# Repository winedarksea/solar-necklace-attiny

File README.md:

# solar-necklace-attiny
Solar Necklace Schematics and ATTiny code

There are two versions here, the original lightsaber necklace and the newer moissanite based version. The attiny code is for the latter.

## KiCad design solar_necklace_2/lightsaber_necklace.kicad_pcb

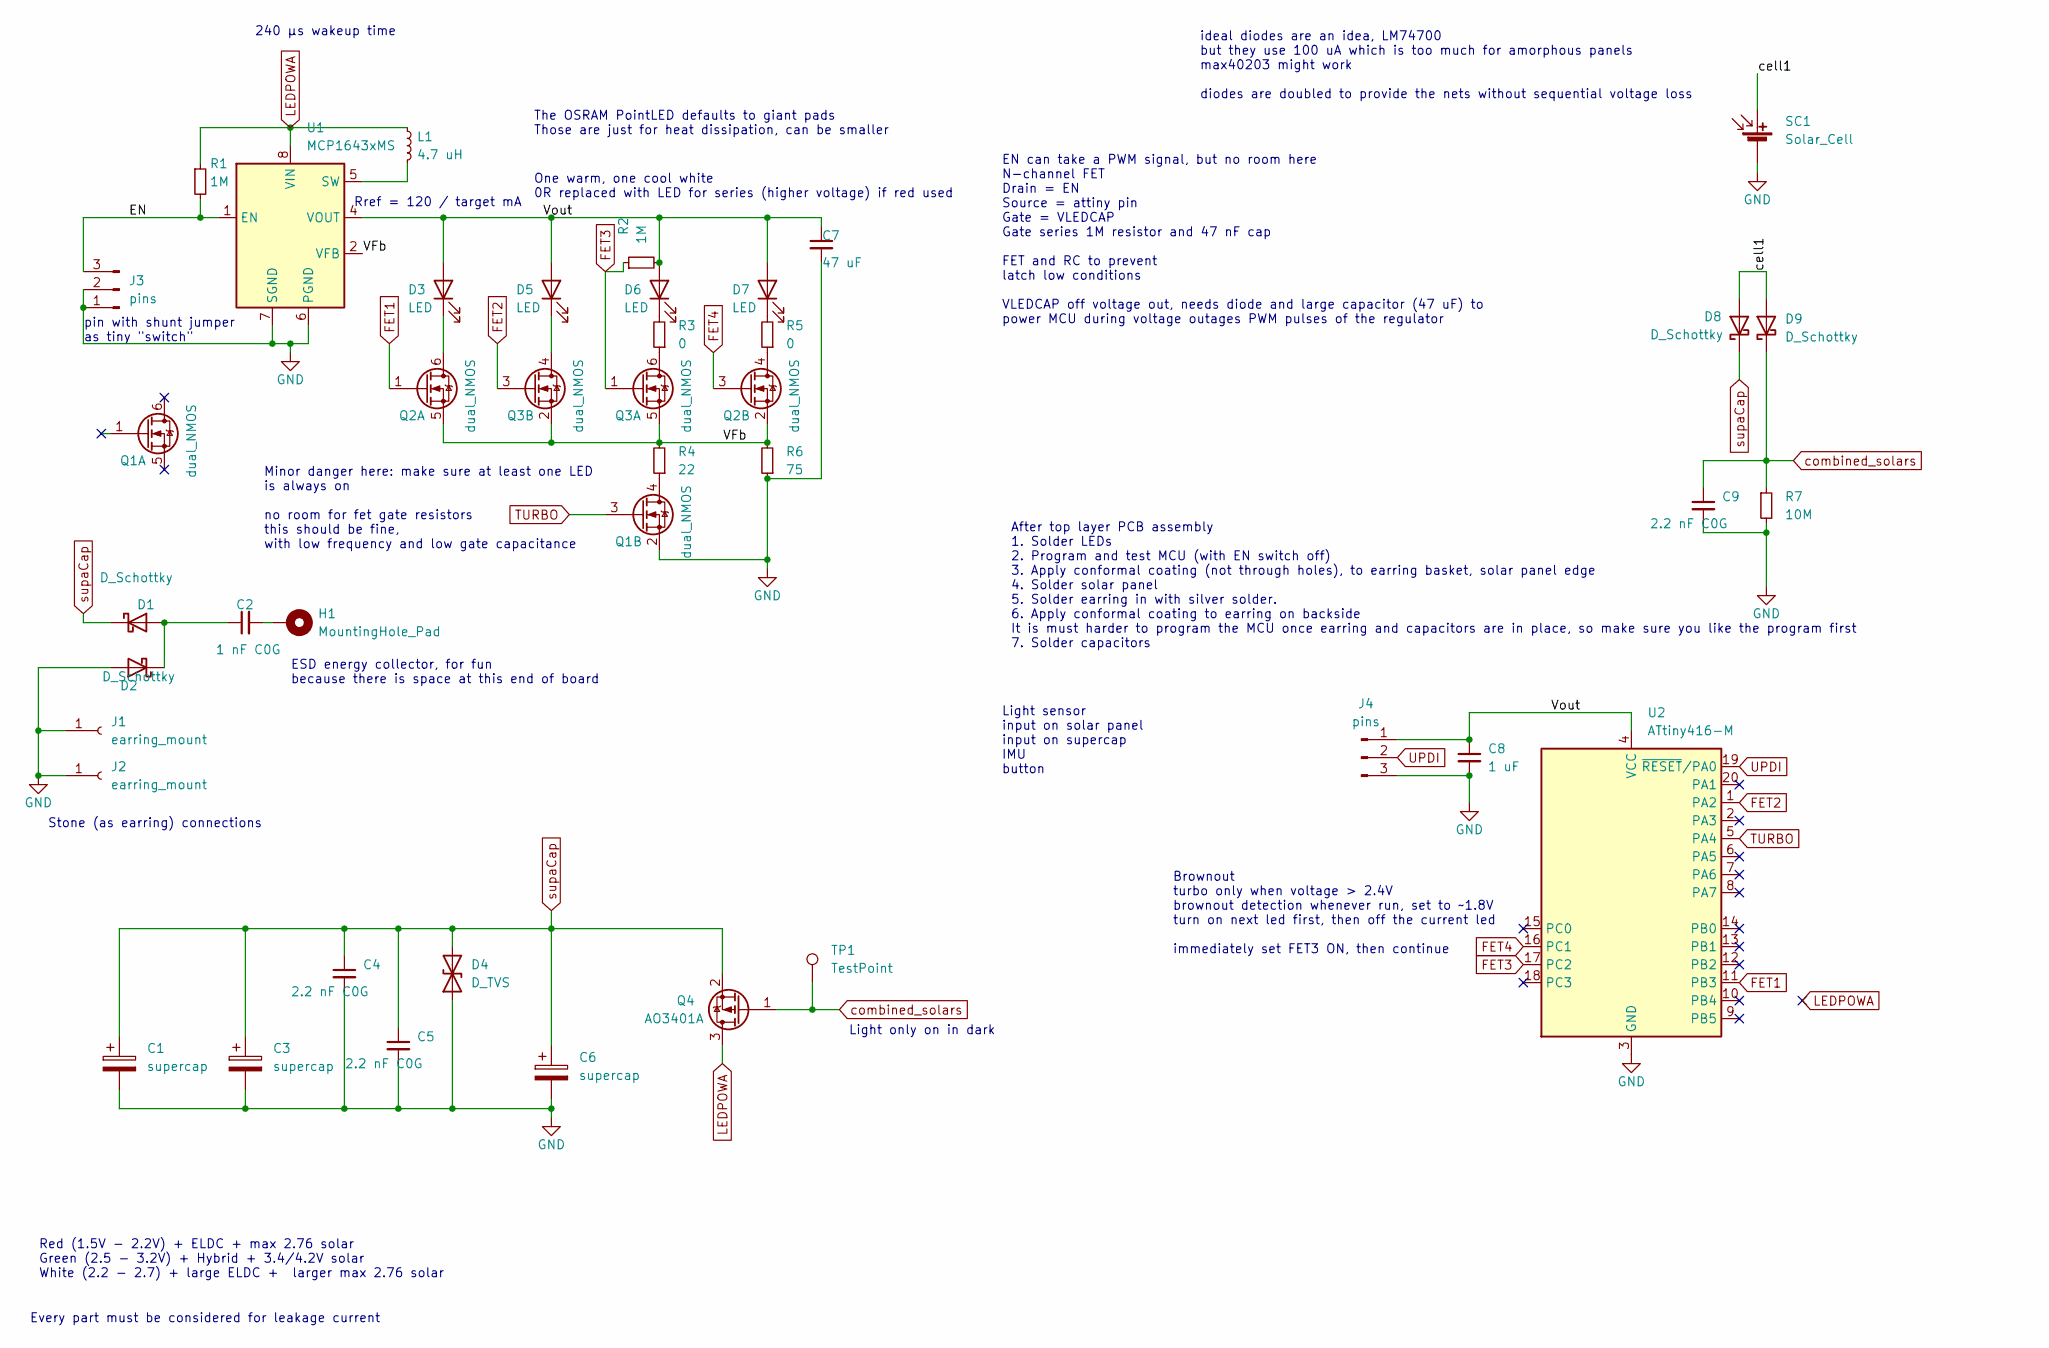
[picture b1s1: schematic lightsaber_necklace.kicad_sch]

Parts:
C1, C3, C6: supercap; C_Rect_L11.5mm_W9.8mm_P10.00mm_MKT
C2: 1 nF C0G; C_1206_3216Metric
C4, C5, C9: 2.2 nF C0G; C_0805_2012Metric
C7: 47 uF; C_1206_3216Metric
C8: 1 uF; C_0402_1005Metric
D1, D2, D8, D9: D_Schottky; D_SOD-323
D3, D5: LED; LED_1206_3216Metric_ReverseMount_Hole1.8x2.4mm
D4: D_TVS; D_SOD-523
D6, D7: LED; LED_Osram_Lx_P47F_D2mm_ReverseMount
H1: MountingHole_Pad; MountingHole_2.2mm_M2_DIN965_Pad
J1, J2: earring_mount; SolderWire-0.5sqmm_1x01_D0.9mm_OD2.1mm
J3, J4: pins; PinHeader_1x03_P1.27mm_Vertical
L1: 4.7 uH; L_0603_1608Metric
Q1, Q2, Q3: dual_NMOS; SOT-23-6
Q4: AO3401A; SOT-23
R1, R2: 1M; R_0402_1005Metric
R3, R5: 0; R_0603_1608Metric
R4: 22; R_0402_1005Metric
R6: 75; R_0603_1608Metric
R7: 10M; R_0402_1005Metric
SC1: Solar_Cell; PinHeader_1x02_P2.00mm_Vertical
TP1: TestPoint; TestPoint_Pad_D1.0mm
U1: MCP1643xMS; MSOP-8_3x3mm_P0.65mm
U2: ATtiny416-M; VQFN-20-1EP_3x3mm_P0.4mm_EP1.7x1.7mm

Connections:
/EN: J3.3, R1.2, U1.1 (EN)
/VFb: Q2.2 (S), Q2.5 (S), Q3.2 (S), Q3.5 (S), R4.2, R6.2, U1.2 (VFB)
/Vout: C7.1, C8.1, D3.2 (A), D5.2 (A), D6.2 (A), D7.2 (A), J4.1, R2.2, U1.4 (VOUT), U2.4 (VCC)
/cell1: D8.2 (A), D9.2 (A), SC1.1 (+)
FET1: Q2.1 (G), U2.11 (PB3)
FET2: Q3.3 (G), U2.1 (PA2)
FET3: Q3.1 (G), R2.1, U2.17 (PC2)
FET4: Q2.3 (G), U2.16 (PC1)
GND: C1.2, C3.2, C4.2, C5.2, C6.2, C7.2, C8.2, C9.2, D2.2 (A), D4.1 (A1), J1.1, J2.1, J3.1, J3.2, J4.3, Q1.2 (S), R6.1, R7.2, SC1.2 (-), U1.6 (PGND), U1.7 (SGND), U2.3 (GND), U2.21 (GND)
LEDPOWA: L1.1, Q4.3 (D), R1.1, U1.8 (VIN)
unnamed: C2.2, H1.1
unnamed: C2.1, D1.2 (A), D2.1 (K)
unnamed: D3.1 (K), Q2.6 (D)
unnamed: D5.1 (K), Q3.4 (D)
unnamed: D6.1 (K), R3.2
unnamed: D7.1 (K), R5.2
unnamed: Q1.4 (D), R4.1
unnamed: Q2.4 (D), R5.1
unnamed: Q3.6 (D), R3.1
unnamed: L1.2, U1.5 (SW)
TURBO: Q1.3 (G), U2.5 (PA4)
UPDI: J4.2, U2.19 (~RESET/PA0)
combined_solars: C9.1, D9.1 (K), Q4.1 (G), R7.1, TP1.1
supaCap: C1.1, C3.1, C4.1, C5.1, C6.1, D1.1 (K), D4.2 (A2), D8.1 (K), Q4.2 (S)

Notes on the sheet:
ideal diodes are an idea, LM74700 but they use 100 uA which is too much for amorphous panels max40203 might work diodes are doubled to provide the nets without sequential voltage loss
Every part must be considered for leakage current
EN can take a PWM signal, but no room here N-channel FET Drain = EN Source = attiny pin Gate = VLEDCAP Gate series 1M resistor and 47 nF cap FET and RC to prevent latch low conditions VLEDCAP off voltage out, needs diode and large capacitor (47 uF) to power MCU during voltage outages PWM pulses of 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
Red (1.5V - 2.2V) + ELDC + max 2.76 solar Green (2.5 - 3.2V) + Hybrid + 3.4/4.2V solar White (2.2 - 2.7) + large ELDC + larger max 2.76 solar
Light only on in dark
The OSRAM PointLED defaults to giant pads Those are just for heat dissipation, can be smaller
Rref = 120 / target mA
After top layer PCB assembly 1. Solder LEDs 2. Program and test MCU (with EN switch off) 3. Apply conformal coating (not through holes), to earring basket, solar panel edge 4. Solder solar panel 5. Solder earring in with silver solder. 6. Apply conformal coating to earring on backside It is must ha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
Minor danger here: make sure at least one LED is always on no room for fet gate resistors this should be fine, with low frequency and low gate capacitance
One warm, one cool white 0R replaced with LED for series (higher voltage) if red used
240 µs wakeup time
Brownout turbo only when voltage > 2.4V brownout detection whenever run, set to ~1.8V turn on next led first, then off the current led immediately set FET3 ON, then continue
Light sensor input on solar panel input on supercap IMU button
pin with shunt jumper as tiny "switch"
Stone (as earring) connections
ESD energy collector, for fun because there is space at this end of board

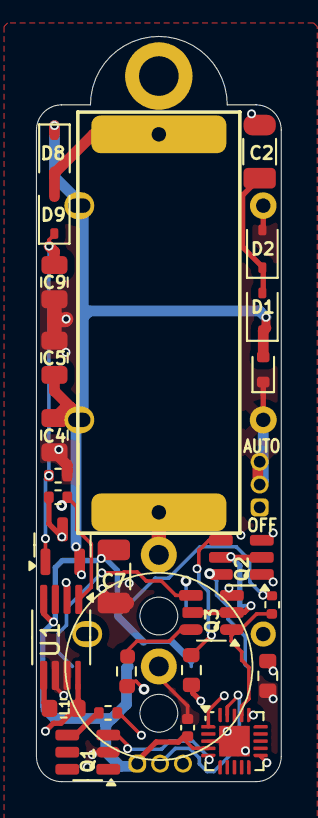
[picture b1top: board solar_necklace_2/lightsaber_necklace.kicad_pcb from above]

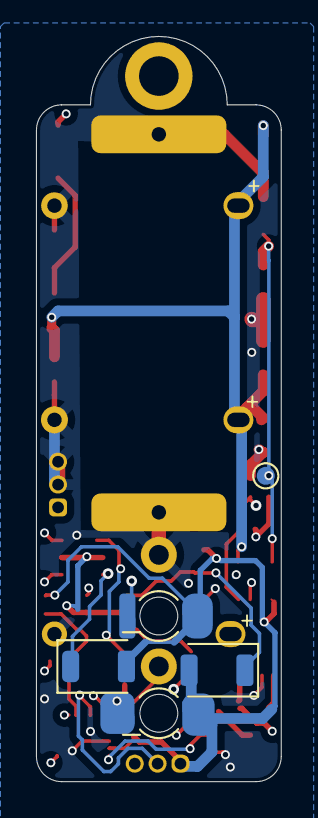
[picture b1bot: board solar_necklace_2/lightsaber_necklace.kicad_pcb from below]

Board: 4 copper layers, 13.6 x 41.4 mm, 39 parts (8 on the bottom side), 24 nets.

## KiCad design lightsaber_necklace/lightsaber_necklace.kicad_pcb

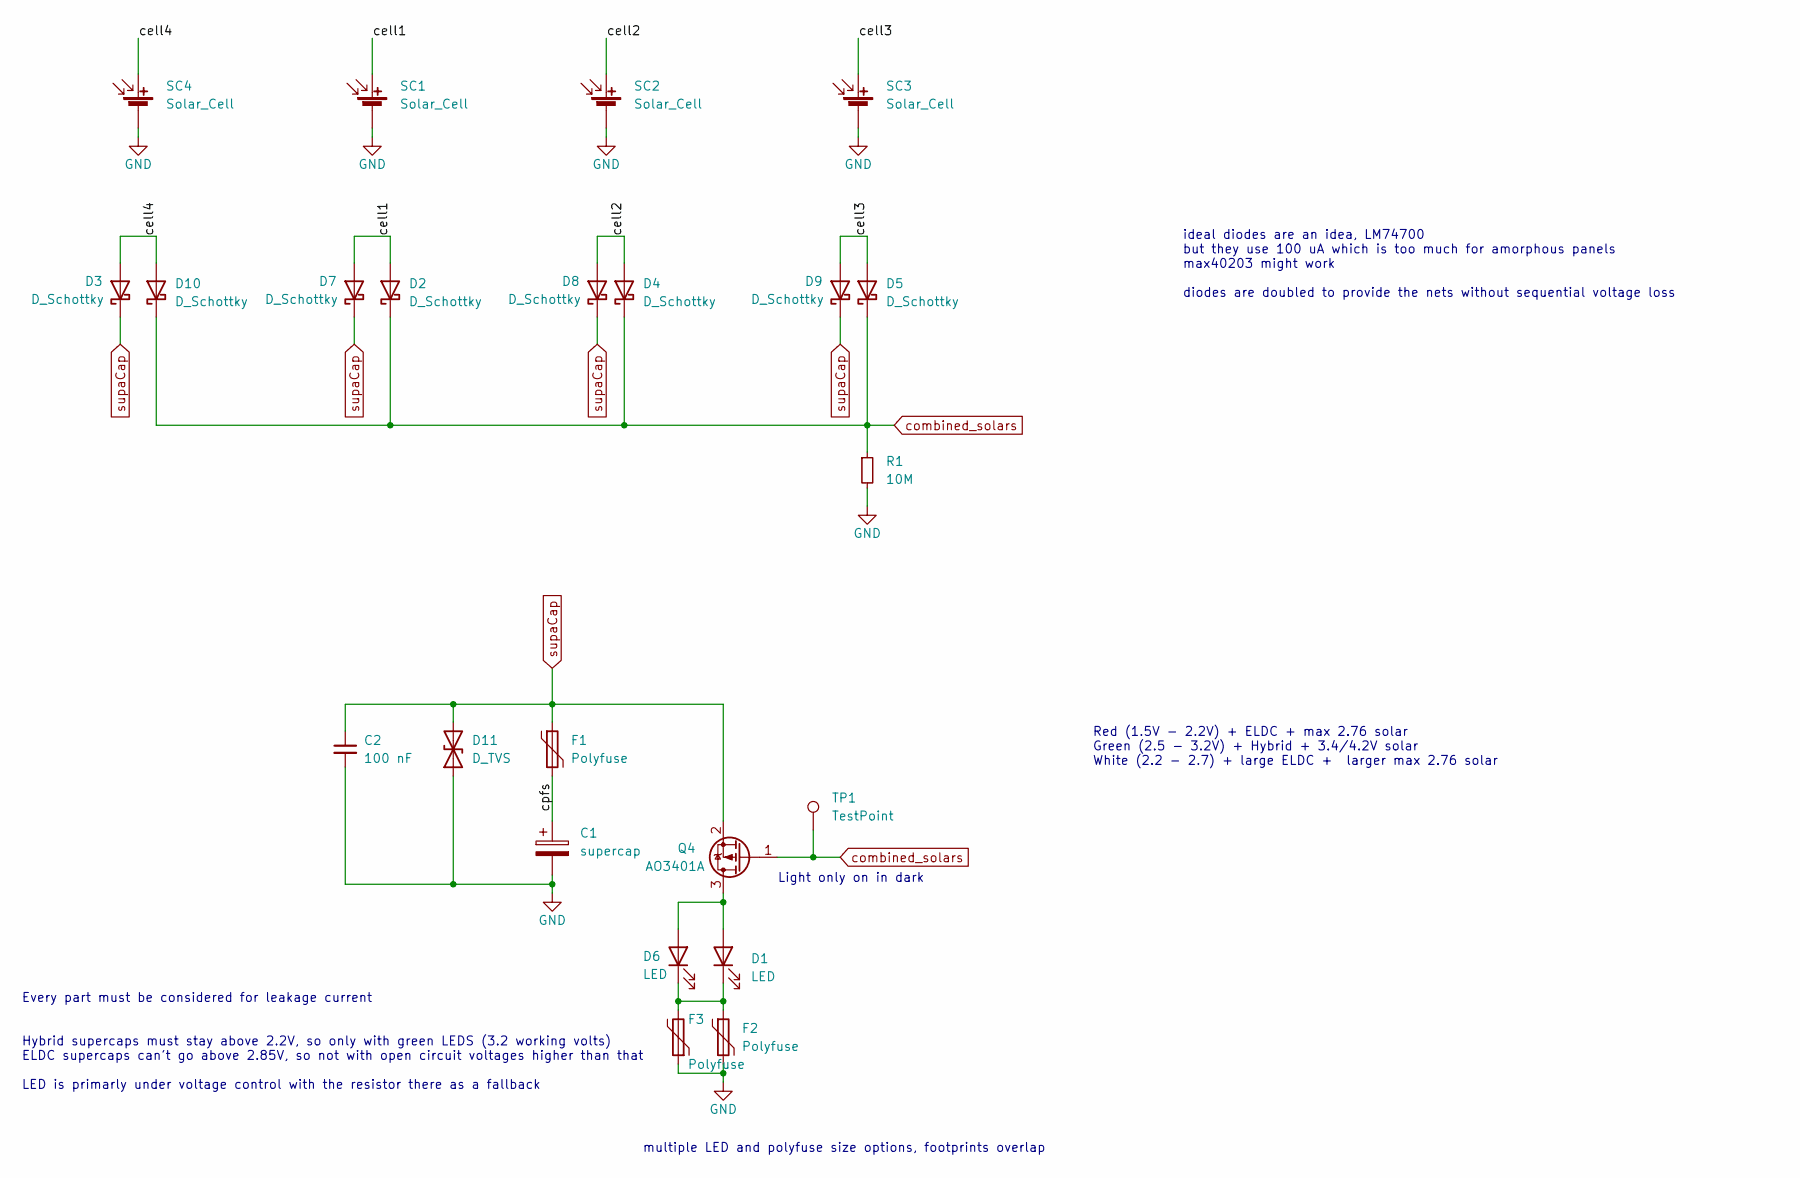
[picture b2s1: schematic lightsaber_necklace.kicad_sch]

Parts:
C1: supercap; C_Radial_D10.0mm_H20.0mm_P5.00mm
C2: 100 nF; C_0402_1005Metric
D1: LED; LED_PLCC_2835
D2, D3, D4, D5, D7, D8, D9, D10: D_Schottky; D_SOD-323
D6: LED; LED_D5.0mm
D11: D_TVS; D_0402_1005Metric
F1: Polyfuse; Fuse_0402_1005Metric_Pad0.77x0.64mm_HandSolder
F2: Polyfuse; R_0201_0603Metric_Pad0.64x0.40mm_HandSolder
F3: Polyfuse; Fuse_0402_1005Metric
Q4: AO3401A; SOT-23
R1: 10M; R_0402_1005Metric
SC1, SC2, SC3, SC4: Solar_Cell; PinHeader_1x02_P2.00mm_Vertical
TP1: TestPoint; TestPoint_Pad_D1.0mm

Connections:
/cell1: D2.2 (A), D7.2 (A), SC1.1 (+)
/cell2: D4.2 (A), D8.2 (A), SC2.1 (+)
/cell3: D5.2 (A), D9.2 (A), SC3.1 (+)
/cell4: D3.2 (A), D10.2 (A), SC4.1 (+)
/cpfs: C1.1, F1.2
GND: C1.2, C2.2, D11.1 (A1), F2.2, F3.1, R1.2, SC1.2 (-), SC2.2 (-), SC3.2 (-), SC4.2 (-)
unnamed: D1.2 (A), D6.2 (A), Q4.3 (D)
unnamed: D1.1 (K), D6.1 (K), F2.1, F3.2
combined_solars: D2.1 (K), D4.1 (K), D5.1 (K), D10.1 (K), Q4.1 (G), R1.1, TP1.1
supaCap: C2.1, D3.1 (K), D7.1 (K), D8.1 (K), D9.1 (K), D11.2 (A2), F1.1, Q4.2 (S)

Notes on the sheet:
ideal diodes are an idea, LM74700 but they use 100 uA which is too much for amorphous panels max40203 might work diodes are doubled to provide the nets without sequential voltage loss
Every part must be considered for leakage current Hybrid supercaps must stay above 2.2V, so only with green LEDS (3.2 working volts) ELDC supercaps can't go above 2.85V, so not with open circuit voltages higher than that LED is primarly under voltage control with the resistor there as a fallback
Red (1.5V - 2.2V) + ELDC + max 2.76 solar Green (2.5 - 3.2V) + Hybrid + 3.4/4.2V solar White (2.2 - 2.7) + large ELDC + larger max 2.76 solar
multiple LED and polyfuse size options, footprints overlap
Light only on in dark

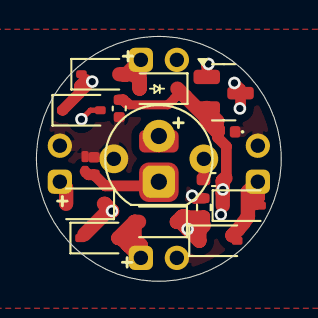
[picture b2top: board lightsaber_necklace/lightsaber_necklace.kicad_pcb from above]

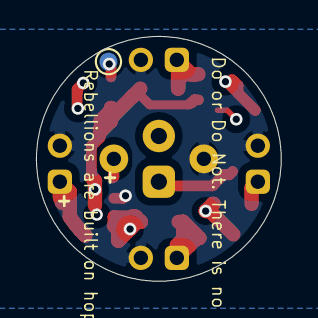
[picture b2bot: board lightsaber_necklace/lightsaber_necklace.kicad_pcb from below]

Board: 4 copper layers, 13.6 x 13.6 mm, 23 parts (2 on the bottom side), 10 nets.

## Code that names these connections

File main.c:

/*
 * ATtiny416 LED Scintillation Firmware
 * Solar-powered moissanite necklace — drives 4 LEDs via NMOS FETs
 * in a pseudo-random pattern to simulate diamond scintillation.
 */

#include <avr/io.h>
#include <avr/interrupt.h>
#include <avr/sleep.h>

/* LED index mapping:
 *   0 = FET1 / PB3
 *   1 = FET2 / PA2
 *   2 = FET3 / PC2  (boot default)
 *   3 = FET4 / PC1
 */
#define BOOT_LED  2

/* ── Global state ────────────────────────────────────────────── */

static uint16_t lfsr = 0xACE1;
static uint8_t  current_led = BOOT_LED;

/* ── PRNG ────────────────────────────────────────────────────── */

static uint8_t prng_next(void)
{
    uint8_t lsb = lfsr & 1;
    lfsr >>= 1;
    if (lsb)
        lfsr ^= 0xB400;   /* maximal-length 16-bit Galois LFSR taps */
    return (uint8_t)lfsr;
}

static uint8_t next_random_led(uint8_t current)
{
    uint8_t next;
    do {
        next = prng_next() & 0x03;
    } while (next == current);
    return next;
}

/* ── LED control ─────────────────────────────────────────────── */

static void led_on(uint8_t idx)
{
    switch (idx) {
    case 0: PORTB.OUTSET = PIN3_bm; break;
    case 1: PORTA.OUTSET = PIN2_bm; break;
    case 2: PORTC.OUTSET = PIN2_bm; break;
    case 3: PORTC.OUTSET = PIN1_bm; break;
    }
}

static void led_off(uint8_t idx)
{
    switch (idx) {
    case 0: PORTB.OUTCLR = PIN3_bm; break;
    case 1: PORTA.OUTCLR = PIN2_bm; break;
    case 2: PORTC.OUTCLR = PIN2_bm; break;
    case 3: PORTC.OUTCLR = PIN1_bm; break;
    }
}

/* ── PIT ISR (wake only) ─────────────────────────────────────── */

ISR(RTC_PIT_vect)
{
    RTC.PITINTFLAGS = RTC_PI_bm;
}

/* ── Initialization ──────────────────────────────────────────── */

static void init_gpio(void)
{
    /* LED gate outputs */
    PORTB.DIRSET = PIN3_bm;              /* PB3 = FET1 */
    PORTA.DIRSET = PIN2_bm;              /* PA2 = FET2 */
    PORTC.DIRSET = PIN1_bm | PIN2_bm;   /* PC1 = FET4, PC2 = FET3 */

    /* PA4, turbo, currently unused — set output-low to prevent floating */
    PORTA.DIRSET = PIN4_bm;

    /* Boot LED on immediately (regulator needs load) */
    led_on(BOOT_LED);

    /* Disable digital input buffers on all pins for power saving.
     * Skip PA0 (UPDI). Outputs don't need them; unused pins must not float. */
    PORTA.PIN1CTRL = PORT_ISC_INPUT_DISABLE_gc;
    PORTA.PIN2CTRL = PORT_ISC_INPUT_DISABLE_gc;
    PORTA.PIN3CTRL = PORT_ISC_INPUT_DISABLE_gc;
    PORTA.PIN4CTRL = PORT_ISC_INPUT_DISABLE_gc;
    PORTA.PIN5CTRL = PORT_ISC_INPUT_DISABLE_gc;
    PORTA.PIN6CTRL = PORT_ISC_INPUT_DISABLE_gc;
    PORTA.PIN7CTRL = PORT_ISC_INPUT_DISABLE_gc;

    PORTB.PIN0CTRL = PORT_ISC_INPUT_DISABLE_gc;
    PORTB.PIN1CTRL = PORT_ISC_INPUT_DISABLE_gc;
    PORTB.PIN2CTRL = PORT_ISC_INPUT_DISABLE_gc;
    PORTB.PIN3CTRL = PORT_ISC_INPUT_DISABLE_gc;
    PORTB.PIN4CTRL = PORT_ISC_INPUT_DISABLE_gc;
    PORTB.PIN5CTRL = PORT_ISC_INPUT_DISABLE_gc;

    PORTC.PIN0CTRL = PORT_ISC_INPUT_DISABLE_gc;
    PORTC.PIN1CTRL = PORT_ISC_INPUT_DISABLE_gc;
    PORTC.PIN2CTRL = PORT_ISC_INPUT_DISABLE_gc;
    PORTC.PIN3CTRL = PORT_ISC_INPUT_DISABLE_gc;
}

static void init_pit(void)
{
    while (RTC.STATUS & RTC_CTRLABUSY_bm)
        ;
    RTC.CLKSEL = RTC_CLKSEL_INT32K_gc;

    while (RTC.STATUS & RTC_CTRLABUSY_bm)
        ;
    RTC.CTRLA = RTC_RUNSTDBY_bm;

    while (RTC.PITSTATUS & RTC_CTRLBUSY_bm)
        ;
    RTC.PITINTCTRL = RTC_PI_bm;

    while (RTC.PITSTATUS & RTC_CTRLBUSY_bm)
        ;
    RTC.PITCTRLA = RTC_PERIOD_CYC8192_gc | RTC_PITEN_bm;

    RTC.PITINTFLAGS = RTC_PI_bm;
}

/* ── Main ────────────────────────────────────────────────────── */

int main(void)
{
    init_gpio();
    init_pit();

    set_sleep_mode(SLEEP_MODE_STANDBY);
    sei();

    while (1) {
        sleep_mode();

        /* Select next LED (guaranteed different from current) */
        uint8_t next = next_random_led(current_led);

        /* Make-before-break: new on, then old off */
        led_on(next);
        led_off(current_led);
        current_led = next;
    }
}

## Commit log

2026-04-12 Build 1: Opus 4.6
2026-04-12 Build 2: desperate power saving measures
2026-04-20 upload schematics
2026-04-20 minor fix that didn't make it to gerbers
